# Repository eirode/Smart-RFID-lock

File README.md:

# Smart-RFID-lock
simple PCB design for Hack Club Half Life that works as an esp32-c3 controlled RFID lock

## Firmware wiring

The firmware uses the MFRC522 reader over SPI:

| RC522 signal | ESP32-C3 GPIO |
| --- | ---: |
| SCK | 8 |
| MISO | 9 |
| MOSI | 10 |
| SDA/SS | 6 |
| RST | 7 |
| 3.3V | 3.3V |
| GND | GND |

The RC522 should remain configured for SPI. The `SDA` pin on an RC522 SPI
module is the SPI chip-select signal, not an I²C data connection.

Before uploading, replace `AUTHORIZED_UID` in
[`Smart-lock firmware/src/main.cpp`](Smart-lock%20firmware/src/main.cpp) with
the UID of the card that should unlock the relay. The relay is energized for
five seconds after an authorized card is detected.

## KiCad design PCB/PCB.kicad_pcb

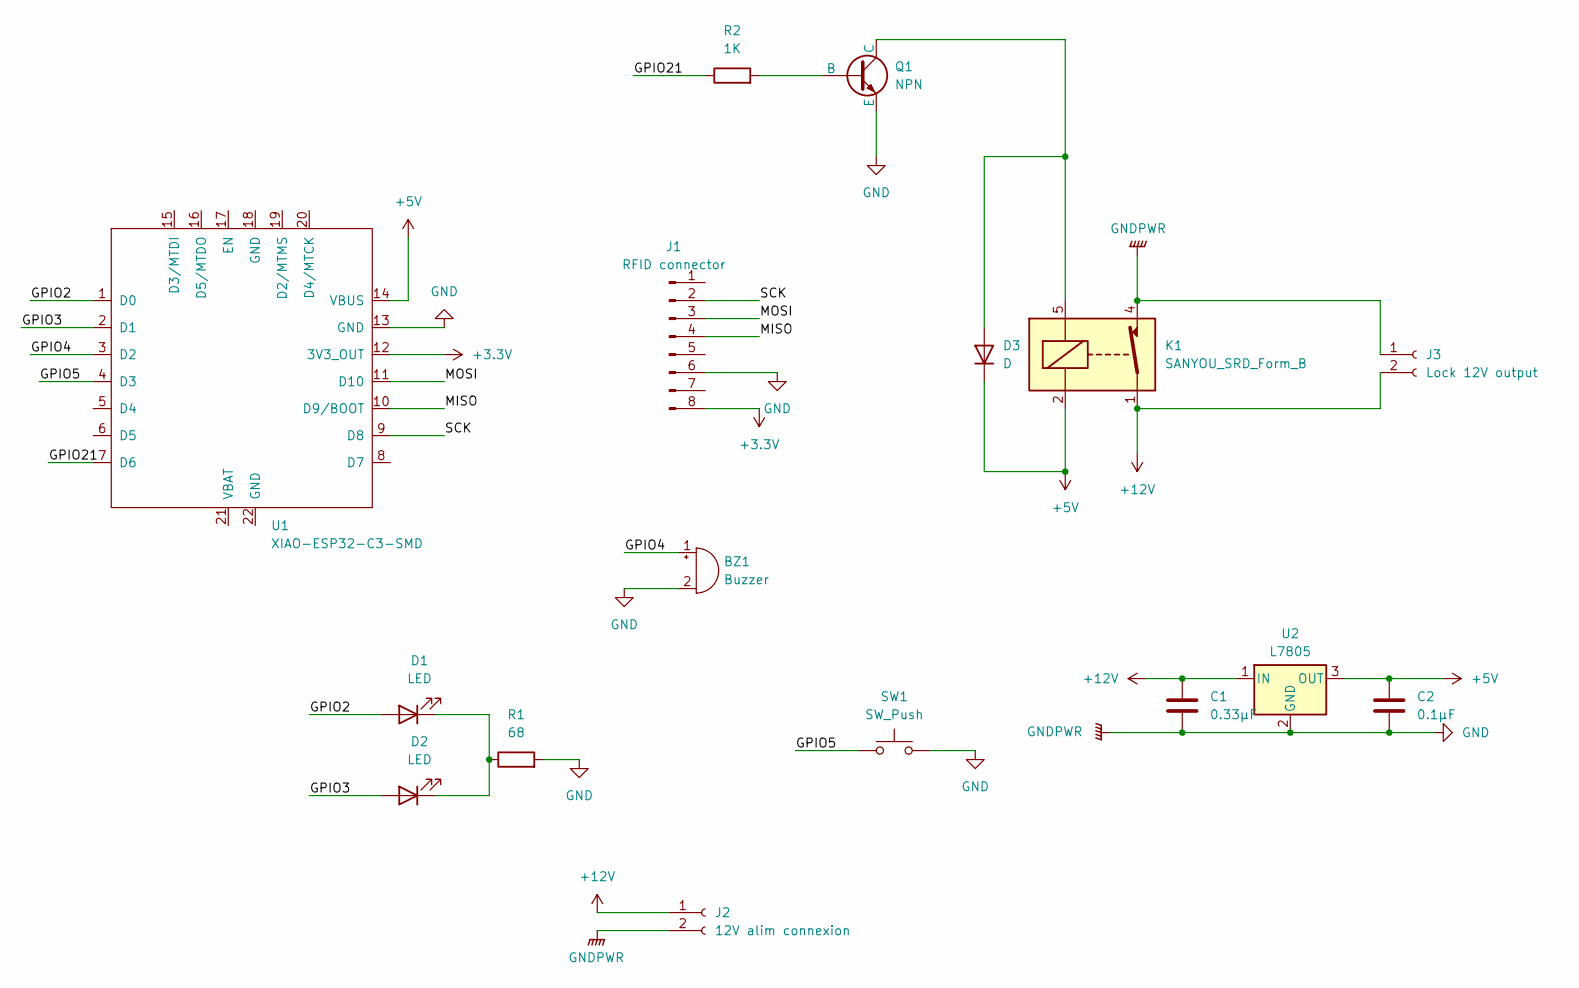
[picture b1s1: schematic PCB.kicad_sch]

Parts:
BZ1: Buzzer; Buzzer_12x9.5RM7.6
C1: 0.33μF; C_Disc_D5.0mm_W2.5mm_P2.50mm
C2: 0.1μF; C_Disc_D5.0mm_W2.5mm_P2.50mm
D1, D2: LED; LED_D1.8mm_W3.3mm_H2.4mm
D3: D; D_DO-15_P15.24mm_Horizontal
J1: RFID connector; PinHeader_1x08_P2.54mm_Vertical
J2: 12V alim connexion; PinSocket_1x02_P2.54mm_Vertical
J3: Lock 12V output; PinSocket_1x02_P2.54mm_Vertical
K1: SANYOU_SRD_Form_B; Relay_SPST_SANYOU_SRD_Series_Form_B
Q1: NPN; PinHeader_1x03_P2.54mm_Vertical
R1: 68; R_Axial_Power_L20.0mm_W6.4mm_P7.62mm_Vertical
R2: 1K; R_Axial_Power_L20.0mm_W6.4mm_P7.62mm_Vertical
SW1: SW_Push; PinHeader_1x02_P2.54mm_Vertical
U1: XIAO-ESP32-C3-SMD
U2: L7805; PinHeader_1x03_P2.54mm_Vertical

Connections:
+3.3V: J1.8, U1.12 (3V3_OUT)
+5V: C2.1, D3.1 (K), K1.2, U1.14 (VBUS), U2.3 (OUT)
+12V: C1.1, J2.1, J3.2, K1.1, U2.1 (IN)
/GPIO2: D1.2 (A), U1.1 (D0)
/GPIO3: D2.2 (A), U1.2 (D1)
/GPIO4: BZ1.1 (+), U1.3 (D2)
/GPIO5: SW1.1, U1.4 (D3)
/GPIO21: R2.1, U1.7 (D6)
/MISO: J1.4, U1.10 (D9/BOOT)
/MOSI: J1.3, U1.11 (D10)
/SCK: J1.2, U1.9 (D8)
GND: BZ1.2 (-), C1.2, C2.2, J1.6, J2.2, J3.1, K1.4, Q1.3 (E), R1.2, SW1.2, U1.13 (GND), U2.2 (GND)
unnamed: D1.1 (K), D2.1 (K), R1.1
unnamed: D3.2 (A), K1.5, Q1.1 (C)
unnamed: Q1.2 (B), R2.2

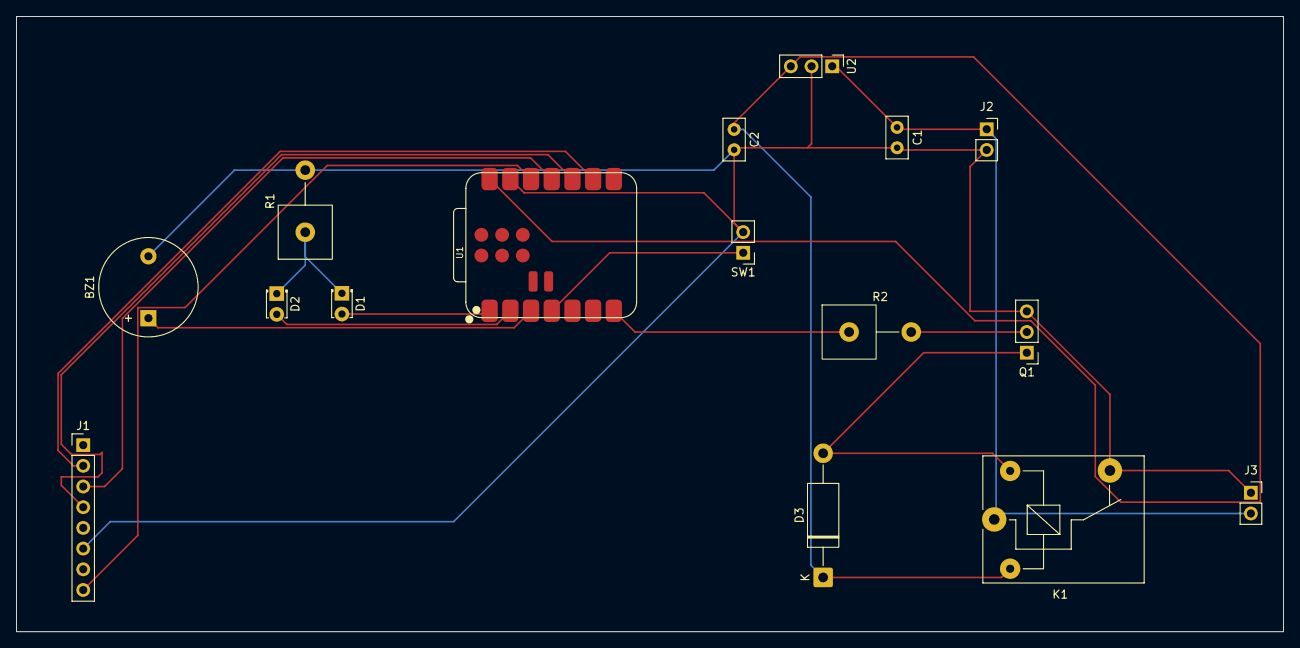
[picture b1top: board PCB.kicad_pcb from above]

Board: 2 copper layers, 155.5 x 75.5 mm, 16 parts (0 on the bottom side), 15 nets.
